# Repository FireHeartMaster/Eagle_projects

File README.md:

# Eagle-projects

Here you have the project and design of a PCB (Printed Circuit Board) of an electromyography device ready to be sent to production, i.e., to be sent to the machines capable of printing these boards.

An electromyography device is an equipment that reads the very small electric signals sent by the brain to control the muscles. This device amplifies these tiny signals so we can use them in pratice, being able to be read by analog-to-digital conversors. Usually electromyography is something mainly of the domain of medicine, but some other applications are rising, which was the case of this project, having been developed for an intern university project that I proposed at my university: École Polytechnique.

While the circuit proposed works fine, as demonstrated in my tests, it's not ready to commercial, industrial nor real medical applications. It was not designed with this intent. However it is indeed the perfect start point for further advances and studies.

Someone that knows this kind of circuit may recognize some of a bit classical small structures in the design. Indeed I used my knowledge of electronics together with some approaches I alreay knew worked in other circuits. I assembled them, made the proper calculations and projected the design you can find here.

Make good use. Good luck

<table>
  <tr>
    <td valign="top"></td>
    <td valign="top"></td>
  </tr>
 </table>

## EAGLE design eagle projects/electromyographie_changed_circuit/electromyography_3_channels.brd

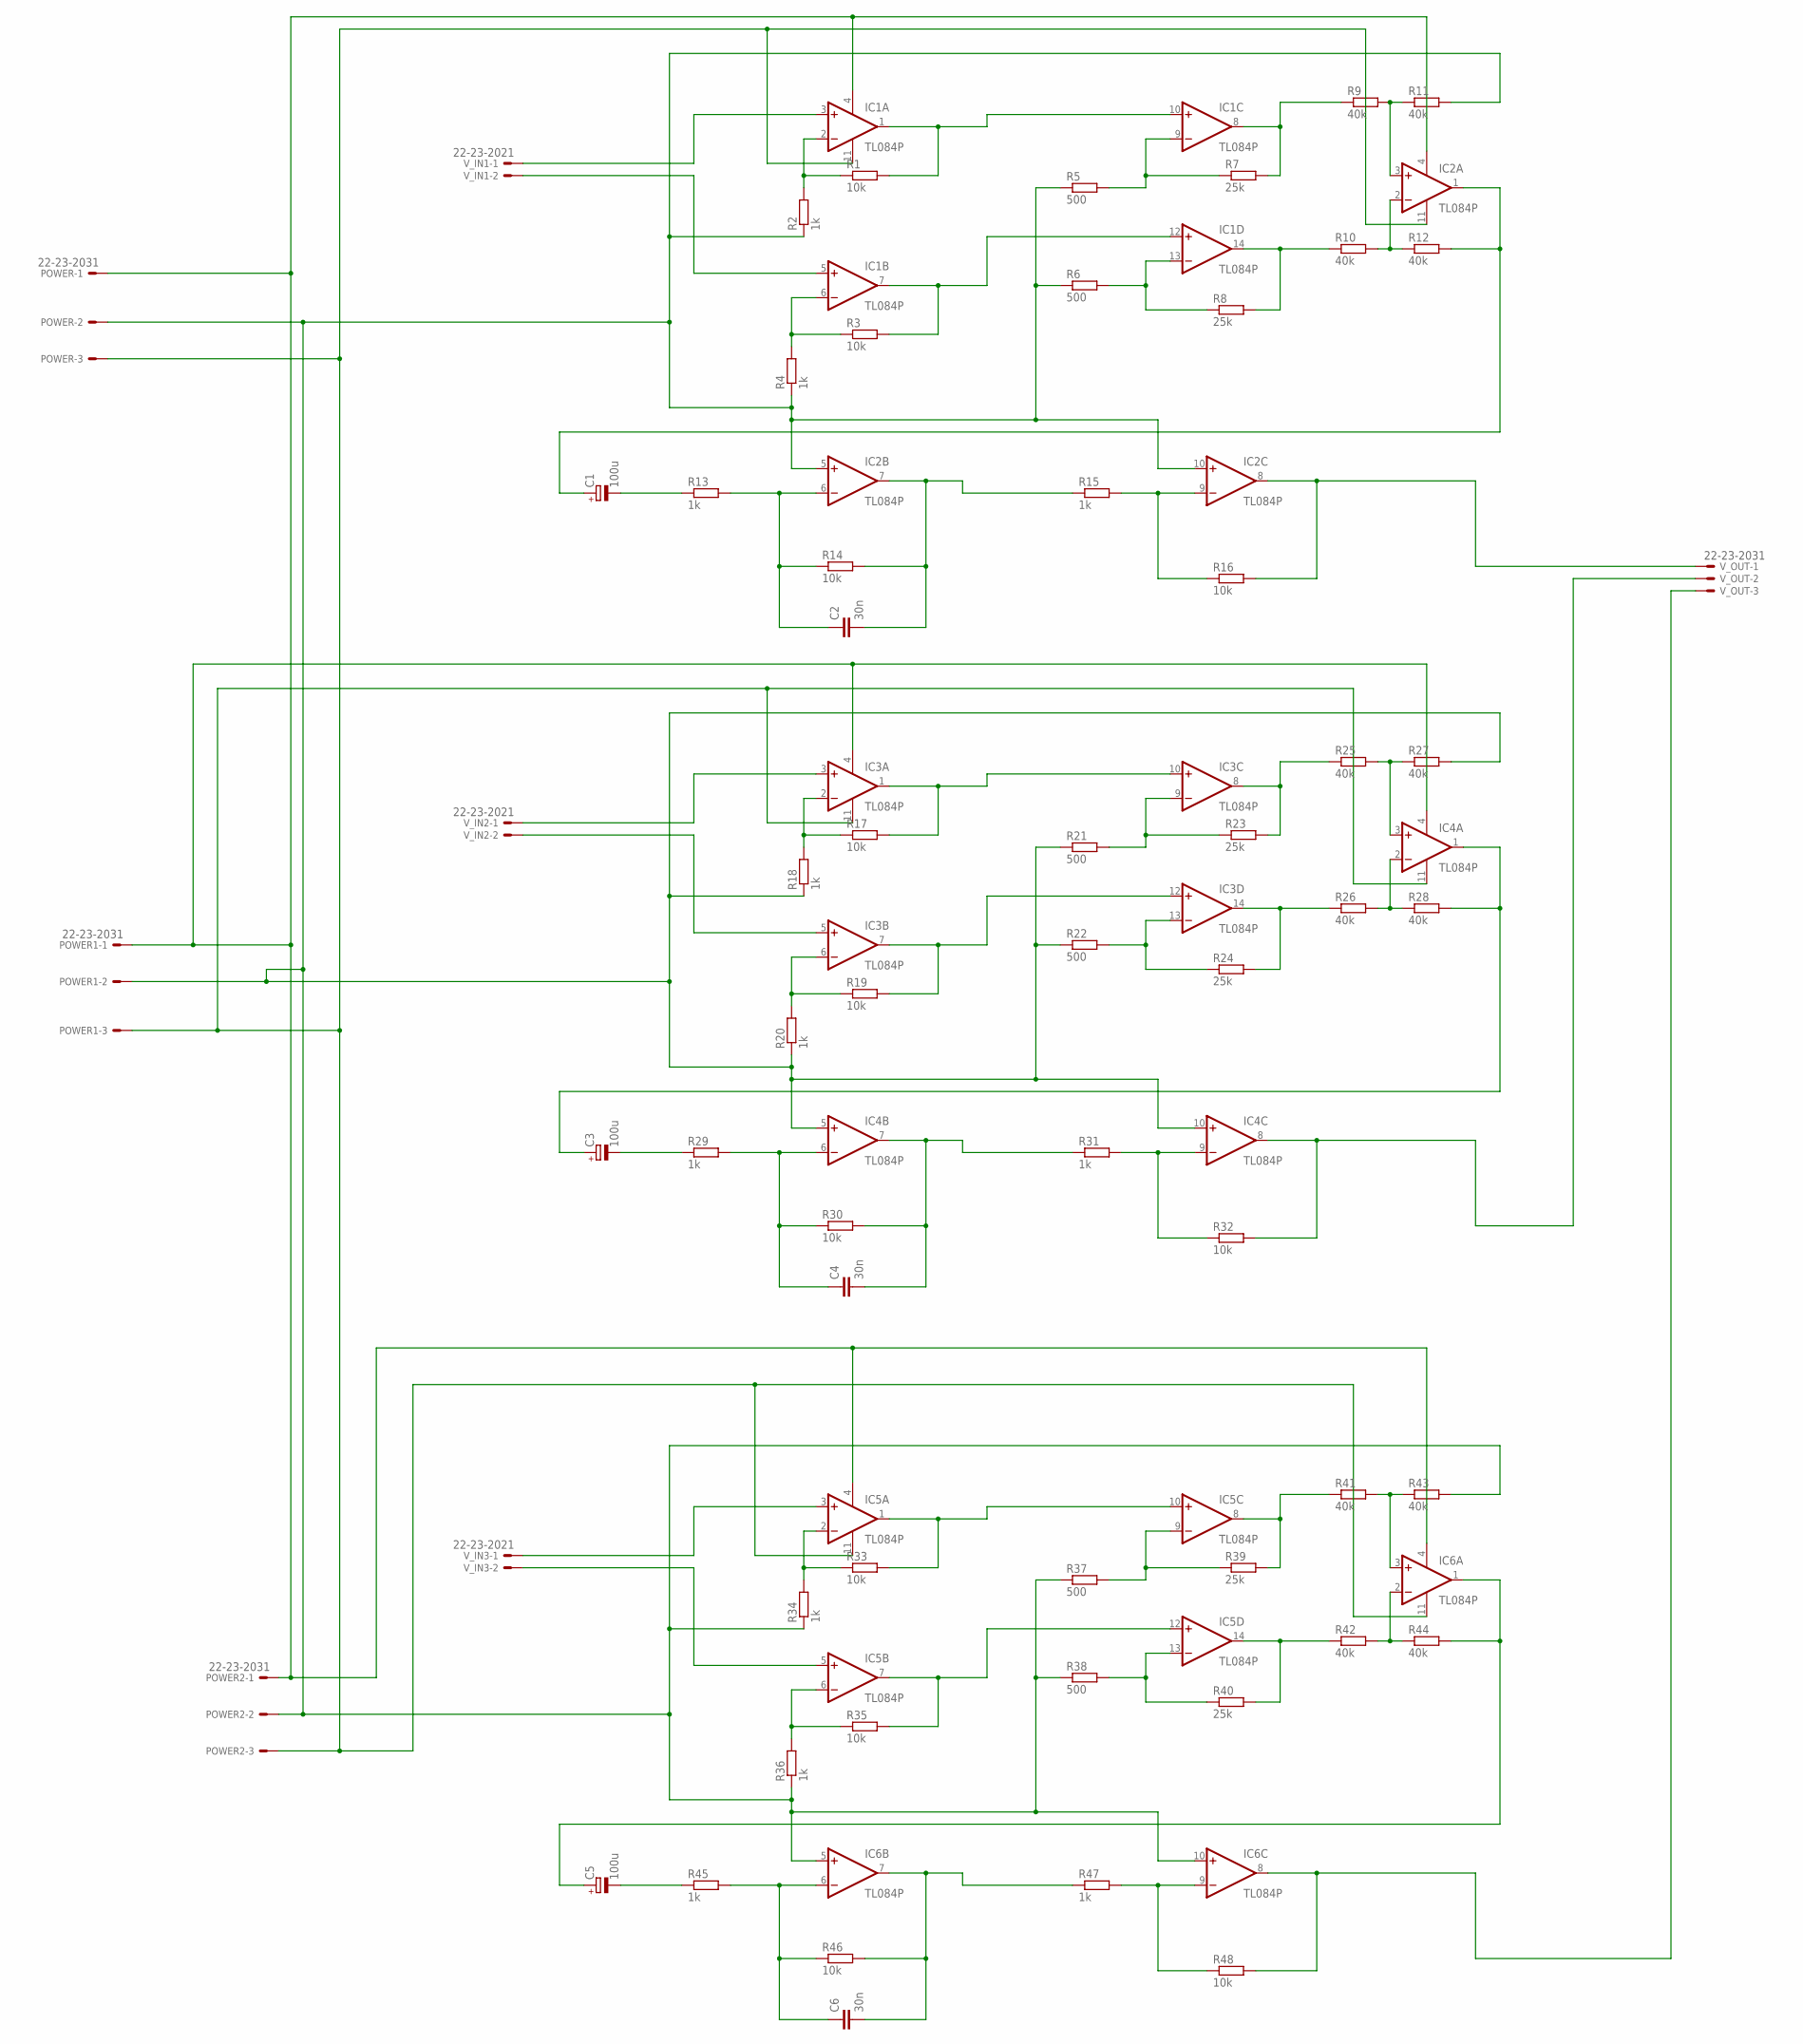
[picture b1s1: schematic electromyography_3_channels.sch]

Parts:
C1, C3, C5: 100u; E3,5-8
C2, C4, C6: 30n; C050-024X044
IC1, IC2, IC3, IC4, IC5, IC6: TL084P; DIL14
POWER, POWER1, POWER2: 22-23-2031
R1, R3, R14, R16, R17, R19, R30, R32, R33, R35, R46, R48: 10k; 0207/10
R2, R4, R13, R15, R18, R20, R29, R31, R34, R36, R45, R47: 1k; 0207/10
R5, R6, R21, R22, R37, R38: 500; 0207/10
R7, R8, R23, R24, R39, R40: 25k; 0207/10
R9, R10, R11, R12, R25, R26, R27, R28, R41, R42, R43, R44: 40k; 0207/10
V_IN1, V_IN2, V_IN3: 22-23-2021
V_OUT: 22-23-2031

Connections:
unnamed: IC1.2 (-IN), R1.1, R2.2
unnamed: IC1.1 (OUT), IC1.10 (+IN), R1.2
unnamed: IC1.9 (-IN), R5.2, R7.1
unnamed: IC1.6 (-IN), R3.1, R4.2
unnamed: IC1.7 (OUT), IC1.12 (+IN), R3.2
unnamed: IC1.13 (-IN), R6.2, R8.1
unnamed: IC1.14 (OUT), R8.2, R10.1
unnamed: IC1.8 (OUT), R7.2, R9.1
unnamed: IC2.2 (-IN), R10.2, R12.1
unnamed: IC2.3 (+IN), R9.2, R11.1
unnamed: C1.+, IC2.1 (OUT), R12.2
unnamed: C1.-, R13.1
unnamed: C2.1, IC2.6 (-IN), R13.2, R14.1
unnamed: C2.2, IC2.7 (OUT), R14.2, R15.1
unnamed: IC2.9 (-IN), R15.2, R16.1
unnamed: IC2.8 (OUT), R16.2, V_OUT.1
unnamed: IC1.3 (+IN), V_IN1.1
unnamed: IC1.5 (+IN), V_IN1.2
unnamed: IC1.4 (V+), IC2.4 (V+), IC3.4 (V+), IC4.4 (V+), IC5.4 (V+), IC6.4 (V+), POWER.1, POWER1.1, POWER2.1
unnamed: IC3.2 (-IN), R17.1, R18.2
unnamed: IC3.1 (OUT), IC3.10 (+IN), R17.2
unnamed: IC3.9 (-IN), R21.2, R23.1
unnamed: IC3.6 (-IN), R19.1, R20.2
unnamed: IC3.7 (OUT), IC3.12 (+IN), R19.2
unnamed: IC3.13 (-IN), R22.2, R24.1
unnamed: IC3.14 (OUT), R24.2, R26.1
unnamed: IC3.8 (OUT), R23.2, R25.1
unnamed: IC4.2 (-IN), R26.2, R28.1
unnamed: IC4.3 (+IN), R25.2, R27.1
unnamed: C3.+, IC4.1 (OUT), R28.2
unnamed: C3.-, R29.1
unnamed: C4.1, IC4.6 (-IN), R29.2, R30.1
unnamed: C4.2, IC4.7 (OUT), R30.2, R31.1
unnamed: IC4.9 (-IN), R31.2, R32.1
unnamed: IC4.8 (OUT), R32.2, V_OUT.2
unnamed: IC2.5 (+IN), IC2.10 (+IN), IC4.5 (+IN), IC4.10 (+IN), IC6.5 (+IN), IC6.10 (+IN), POWER.2, POWER1.2, POWER2.2, R2.1, R4.1, R5.1, R6.1, R11.2, R18.1, R20.1, R21.1, R22.1, R27.2, R34.1, R36.1, R37.1, R38.1, R43.2
unnamed: IC3.3 (+IN), V_IN2.1
unnamed: IC3.5 (+IN), V_IN2.2
unnamed: IC5.2 (-IN), R33.1, R34.2
unnamed: IC5.1 (OUT), IC5.10 (+IN), R33.2
unnamed: IC5.9 (-IN), R37.2, R39.1
unnamed: IC5.6 (-IN), R35.1, R36.2
unnamed: IC5.7 (OUT), IC5.12 (+IN), R35.2
unnamed: IC5.13 (-IN), R38.2, R40.1
unnamed: IC5.14 (OUT), R40.2, R42.1
unnamed: IC5.8 (OUT), R39.2, R41.1
unnamed: IC6.2 (-IN), R42.2, R44.1
unnamed: IC6.3 (+IN), R41.2, R43.1
unnamed: C5.+, IC6.1 (OUT), R44.2
unnamed: C5.-, R45.1
unnamed: C6.1, IC6.6 (-IN), R45.2, R46.1
unnamed: C6.2, IC6.7 (OUT), R46.2, R47.1
unnamed: IC6.9 (-IN), R47.2, R48.1
unnamed: IC6.8 (OUT), R48.2, V_OUT.3
unnamed: IC1.11 (V-), IC2.11 (V-), IC3.11 (V-), IC4.11 (V-), IC5.11 (V-), IC6.11 (V-), POWER.3, POWER1.3, POWER2.3
unnamed: IC5.3 (+IN), V_IN3.1
unnamed: IC5.5 (+IN), V_IN3.2

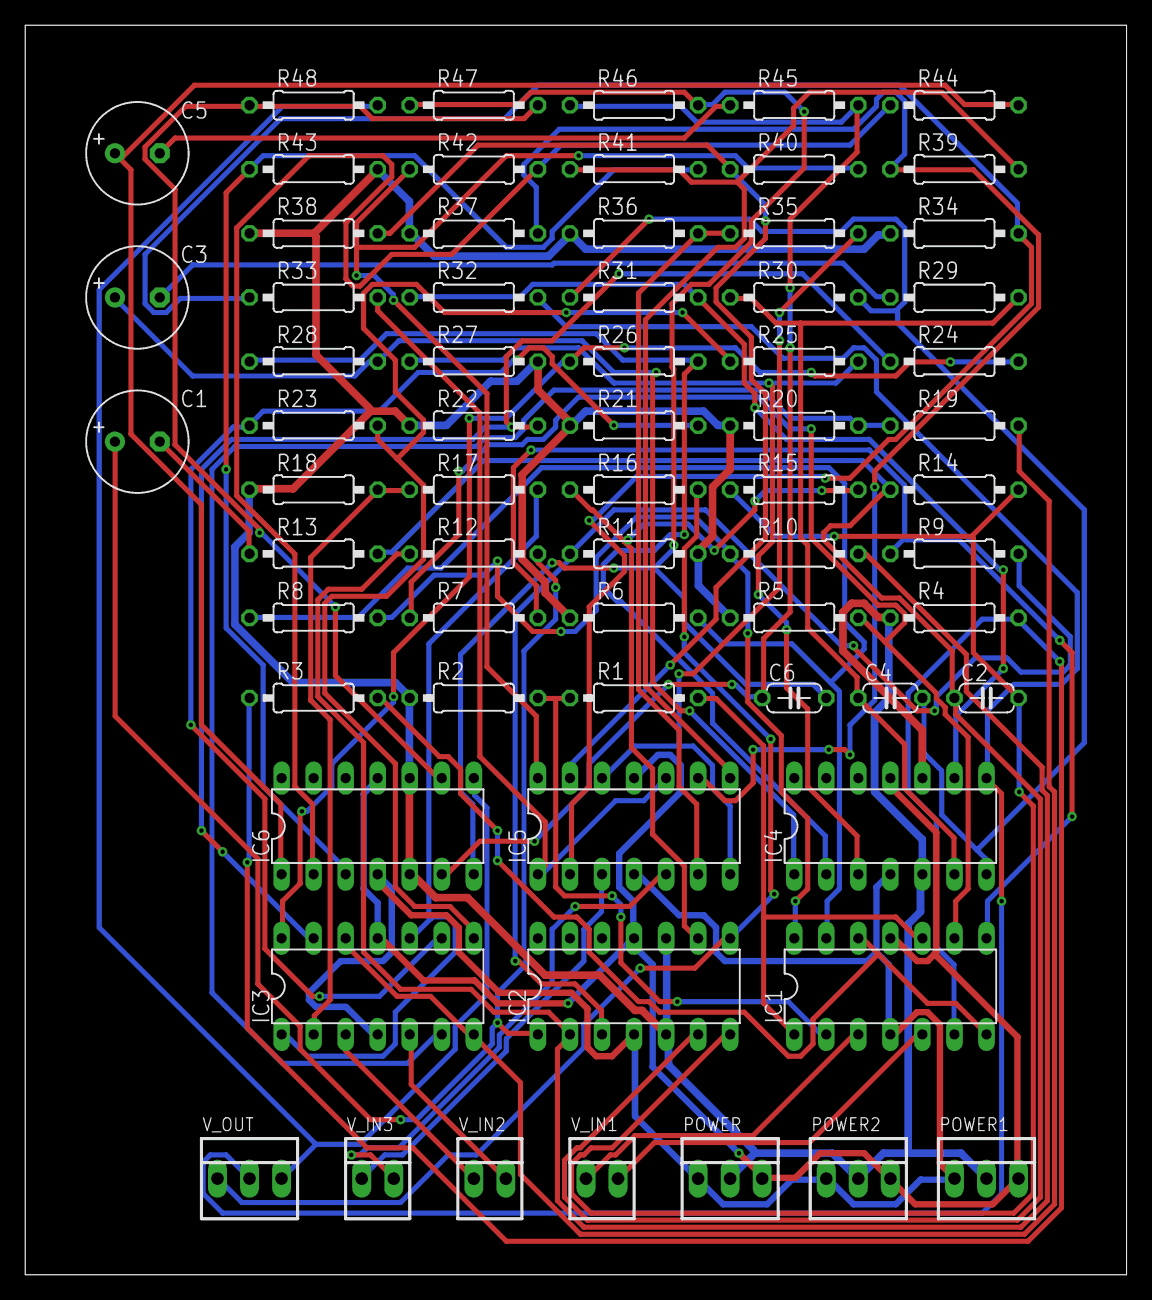
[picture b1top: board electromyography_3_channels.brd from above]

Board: 2 copper layers, 87.3 x 99.0 mm, 67 parts (0 on the bottom side), 57 nets.

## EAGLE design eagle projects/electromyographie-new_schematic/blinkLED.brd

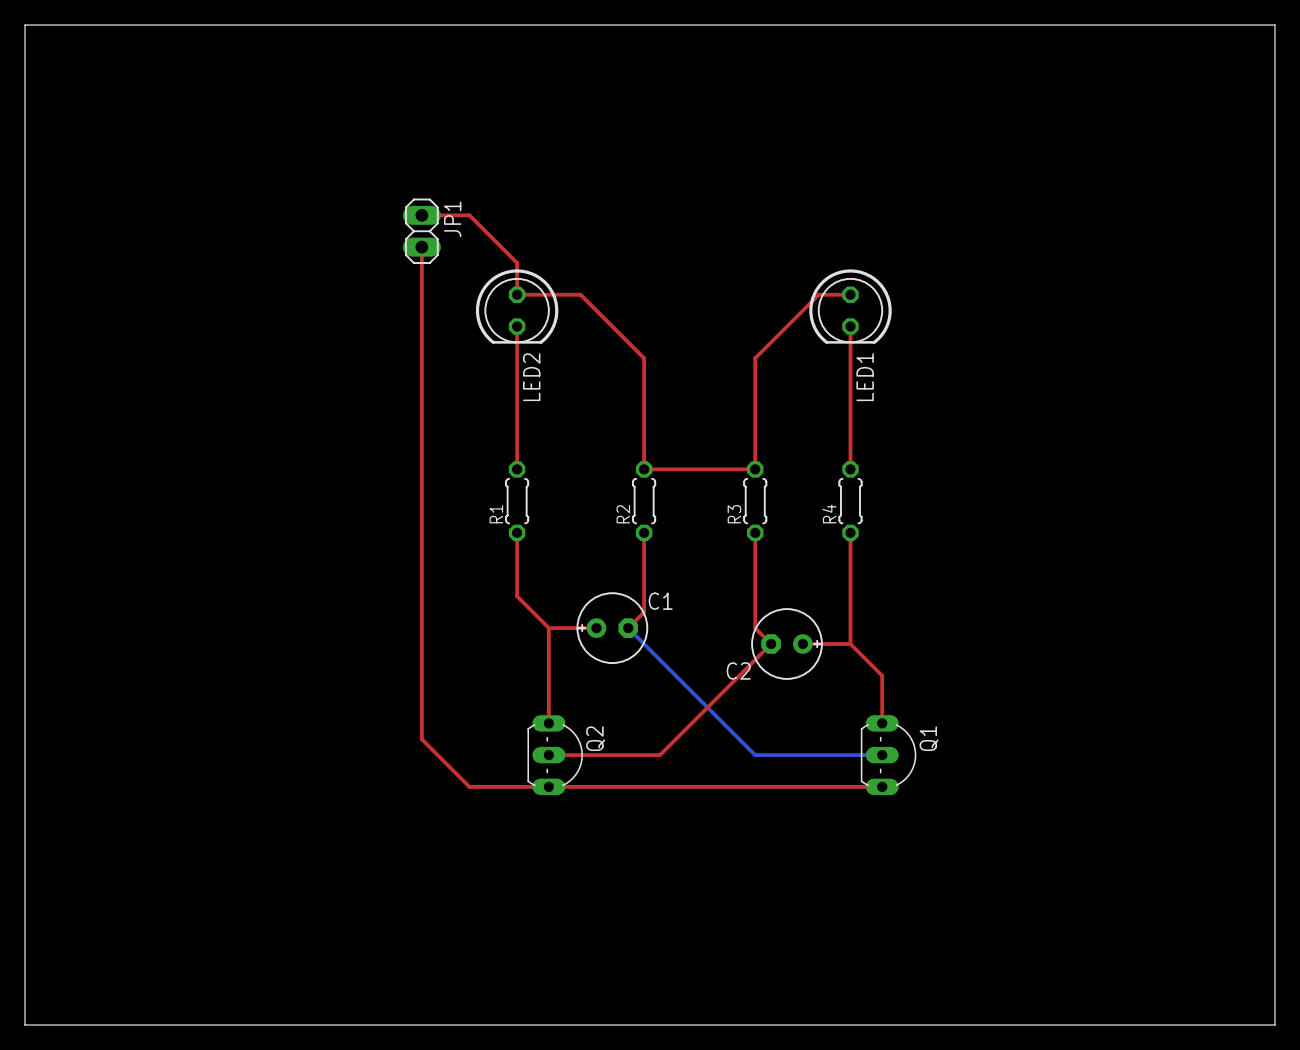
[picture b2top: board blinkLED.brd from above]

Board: 2 copper layers, 100.0 x 80.0 mm, 11 parts (0 on the bottom side), 8 nets.

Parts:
C1, C2: 10µ; E2,5-6E
JP1: 9V; 1X02
LED1, LED2: RED; LED5MM
Q1, Q2: BC548; TO92-EBC
R1, R4: 470; 0204/5
R2, R3: 47k; 0204/5

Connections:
unnamed: C2.-, Q2.B, R3.1
unnamed: C1.-, Q1.B, R2.1
unnamed: JP1.2, Q1.E, Q2.E
unnamed: C1.+, Q2.C, R1.1
unnamed: C2.+, Q1.C, R4.1
unnamed: LED2.K, R1.2
unnamed: LED1.K, R4.2
unnamed: JP1.1, LED1.A, LED2.A, R2.2, R3.2

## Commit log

2018-11-06 First Commit
    Projects as in their original versions
2020-07-24 Added pictures of the circuit
    Added pictures of the circuit design I created and of the circuit after I assembled all the pieces and electronic components
2020-07-24 Added picture with circuit schematic only
